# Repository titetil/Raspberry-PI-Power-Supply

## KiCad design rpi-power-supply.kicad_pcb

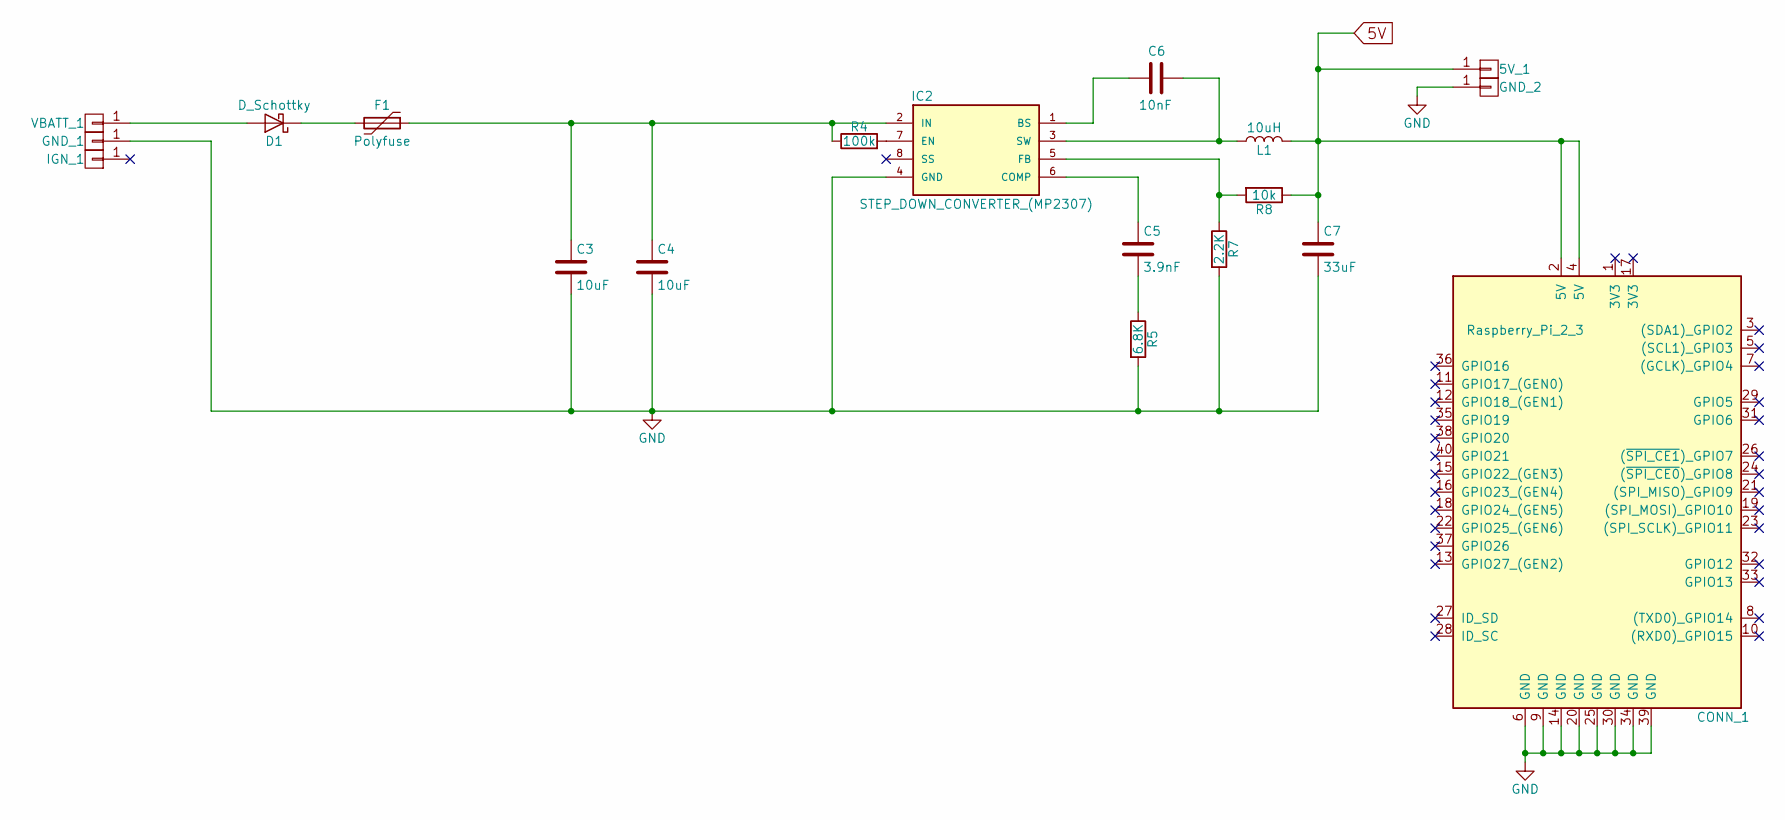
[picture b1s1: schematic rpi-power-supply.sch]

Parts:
5V_1: CONN_01X01; 2mm_X_3mm_WIRE_PAD
C3, C4: 10uF; C_1206
C5: 3.9nF; C_0805
C6: 10nF; C_0805
C7: 33uF; C_1206
CONN_1: Raspberry_Pi_2_3; 40-PIN_SMD_(M20-7812045)
D1: D_Schottky; DO-214AB
F1: Polyfuse; R_1812
GND_1, GND_2: CONN_01X01; 2mm_X_3mm_WIRE_PAD
IC2: STEP_DOWN_CONVERTER_(MP2307); SOIC8N_(EXPOSED_PAD)
IGN_1: CONN_01X01; 2mm_X_3mm_WIRE_PAD
L1: 10uH; INDUCTOR_10uH_(ASPI-0630LR)
R4: 100k; R_0805
R5: 6.8K; R_0805
R7: 2.2K; R_0805
R8: 10k; R_0805
VBATT_1: CONN_01X01; 2mm_X_3mm_WIRE_PAD

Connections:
5V: 5V_1.1, C7.1, CONN_1.2 (5V), CONN_1.4 (5V), L1.2, R8.1
GND: C3.2, C4.2, C7.2, CONN_1.6 (GND), CONN_1.9 (GND), CONN_1.14 (GND), CONN_1.20 (GND), CONN_1.25 (GND), CONN_1.30 (GND), CONN_1.34 (GND), CONN_1.39 (GND), GND_1.1, GND_2.1, IC2.4 (GND), IC2.9 (GND), R5.2, R7.2
unnamed: C3.1, C4.1, F1.1, IC2.2 (IN), R4.1
unnamed: C5.1, IC2.6 (COMP)
unnamed: C5.2, R5.1
unnamed: C6.1, IC2.3 (SW), L1.1
unnamed: C6.2, IC2.1 (BS)
unnamed: D1.1 (K), F1.2
unnamed: D1.2 (A), VBATT_1.1
unnamed: IC2.5 (FB), R7.1, R8.2
unnamed: IC2.7 (EN), R4.2

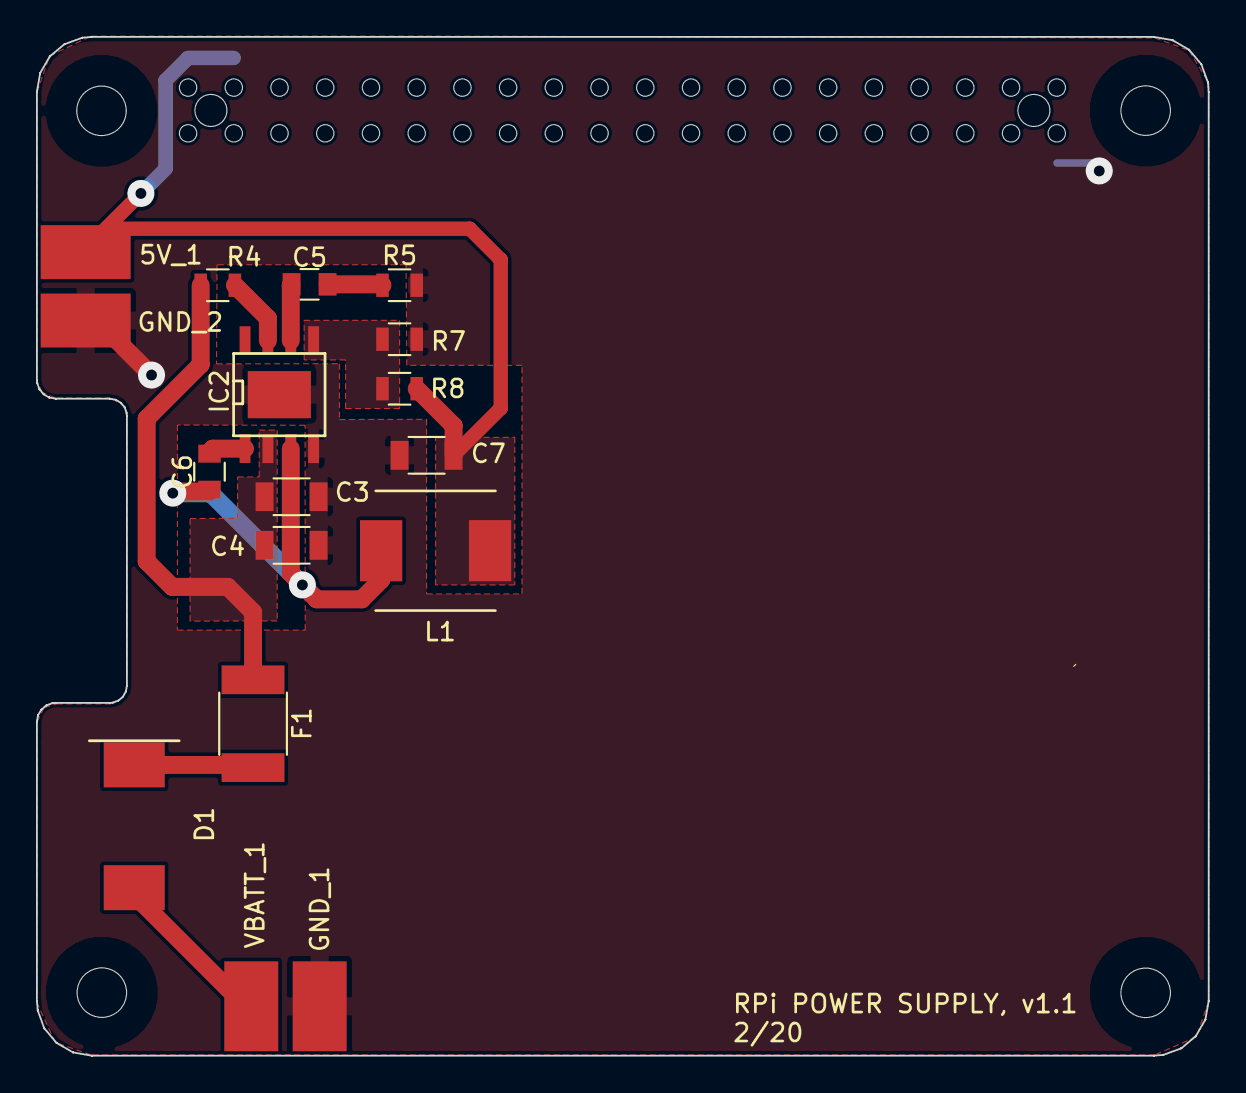
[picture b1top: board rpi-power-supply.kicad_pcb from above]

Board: 2 copper layers, 65.1 x 56.6 mm, 18 parts (1 on the bottom side), 11 nets.

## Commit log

2020-02-14 Init Commit
